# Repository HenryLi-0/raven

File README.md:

<div align="center">
    <h2>Raven</h2>
    <p>by <a href= "https://github.com/HenryLi-0/raven"> @HenryLi-0 </a></p>
    
</div>

<sub>It's open sourced! Hardware licensed under CERN OHL S v2. Software licensed under GNU GPL v3.</sub>

---

## Raven

[Raven](https://github.com/HenryLi-0/raven/) is an open source spinning LED light display, built for (and generously funded by) Hack Club's [Highway](https://highway.hackclub.com/)!

## Introduction
Since being introduced to an LED strip during FRC at the start of 2024, I realized I really like LEDs. Like a little too much. This could also be seen with the 10 LEDs from my [Hackpad](https://github.com/hackclub/hackpad/pull/224) back in October 2024 and when I brought it on a robotics trip to BattleCry in June 2025 (iykyk). Simply, I kinda like LEDs a lot. 

Now inspired by the lights at the venue of the aforementioned robotics trip (and the lights show that occured near the end of the event), that brings us here! Introducting Raven, a spinning LED display that uses 50 LEDs spread across 5 panels, spinning *really* fast. Using a Hall Effect Sensor for speed measurement, the measured values for angular prediction, and wireless control for wireless communications, Raven is capable of producing sector-based effects, rainbow gradients, strobes, and more, with a full 360 degree range of the room, or any sector of it! Apart from being an almost disco ball of sorts, the mechanism itself allows it to also act as an LED light display, almost looking like some sort of Vegas Sphere, except as a cylinder.

This project took over a hundred hours to make (with tons of redesigns!), and, retrospectively, I guess it's just because I think LEDs look pretty cool. The idea of replicating what happened in the venue really kept me going, and, now staring at what's been created, I think those hours were worth it! Learned lots a things along the way, such as reading datasheets, power in general, and implementing stuff from the ground up!

## Long Description

Incase you wanted a full, long description, here it is!

Introducing Raven, an open source spinning LED light display! The system can be separated into three parts: the motor subsystem, the LED control subsystem, and the LED panels. But first, what exactly is the idea behind Raven? Inspired by the light effects done at BattleCry 2025 at WPI (2025BC), along with really liking LEDs for some reason, I wanted to create a LED display that lights up an entire room. But a stationary system wouldn't create the desired effect, the effect to slice up the room into different colors. For example, imagine the left side of the room being red and the right being blue.

This is accomplished by having 5 LED panels, each with 10 LEDs each, vertically stacked, pointing outwards. These 5 panels form a 180 degree circle, each panel spaced 45 degrees off the next. Arms connecting to the top and bottom of the LED panels attach to a center. Spacers keep these top and bottom arms in position. In the center, the top arms connect to the LED control PCB, which contains a XIAO ESP32-C3. This board is also equipped with a Hall Effect Sensor, used to be a simple way to measure RPM without an expensive encoder. This entire section spins on a shaft collar connected to a 775 motor. Additionally, a 18650 Li-ion battery is on this section, powering the whole thing without need for a power wire.

In order to save on costs, a slip ring was strongly avoided during design. Instead, the motor subsystem powers the motor with 4 Li-ion batteries, supplying a total of 14.8-16.8V @20A to the motor. 4 Li-ion batteries was choosen as a solution to the problem with finding suitable boost converters, which were either incapable of handling 20A, or are just really expensive. In fact, it is actually cheaper to use 4 Li-ion batteries than a single one of these boost converters. This solution also gave the benefit of having additional battery time, which was a nice side bonus. The motor subsystem is stationary, with the base being a copy of the LED control subsystem's PCB. This empty PCB is used as the FR-4 material of the PCB is likely stronger than PLA parts, while also being a smart way to reuse the multiple PCBs sent by JLCPCB. This is also the reason why there are 5 LED panels, as to minimize waste. The motor subsystem is also powered with a XIAO ESP32-C3, and has its own Hall Effect Sensor to measure the RPM of the LED subsystem.

The control system starts at the stationary motor subsystem microcontroller, which sends a constant ping to the LED subsystem's microcontroller. The LED subsystem reads this ping through the ESP32's bluetooth capabilities, and also sends a ping back. Both systems need to listen to each other in order to think they are operating properly. In the event that a ping isn't heard in a long time, the LED subsystem will stop operating and the motor subsystem will attempt to bring the motor to a stop. While operating properly, the LED subsystem uses a mix of data from the motor subsystem's Hall Effect Sensor and the LED subsystem's Hall Effect Sensor to calculate its speed and position, utilizing a model of the motor's speed. The motor subsystem will use PID control with a MOSFET to ensure that the LED subsystem reaches the proper spin.

This entire system is packaged inside a cylinderical shape with diameter of roughly 24 cm and a height of roughly 15 cm. The LED subsystem, weighing less than 2 pounds, plans to spin at anywhere from 1k-2k RPM, in order to achieve a speed where the LEDs essentially blend into a blur. The LED subsytem is loaded with almost 120 screws, in order to ensure that the LED subsystem stays in place. Additionally, all batteries are protected inside an over-discharge protection board and charged with a TP4056 module with protection (the TP4056 does NOT provide power to the system, it is only used for charging.).

And that's Raven, an open source spinning light display!

## Directory

Wanna know more? Here's some quick places to get started!

- [CAD](</CAD/README.md>)
    - We used OnShape for this, but you can grab files here too! (Although, poking around the CAD is probably better to have an idea of what things look like!)
- [PCB](</PCB/README.md>)
    - We have three different PCBs, have a look at them! They were created in KiCad v8.0.8 (yeah I know I'm a whole major version behind.)
- [Firmware](</firmware/README.md>)
    - We have two firmwares, one for each subsystem! (These firmwares are written for CircuitPython! Look here for deeper instructions!)
- [Journal](</JOURNAL.md>)
    - Wanna know the thought process behind stuff? Or just a really long read? Check out the journal! (or the [`updatelogs`](/updatelogs/) for everything in different files...)
- [BOM](</BOM.csv>)
    - Wanna make your own copy of Raven? Here's the BOM in CSV format! (You can look at [`BOM.md`](</BOM.md>) for a markdown version of it, but it won't be too descriptive!) (Or just scroll down.)

---

---

## Assembly!

1. First things first, it's recommended that you pull up the [CAD](</CAD/README.md>) and get familiar with how things look, and think of the order of steps. Special attention should be paid towards making sure that it is possible to put together, along with wires being able to "fit". Use logic to figure out whether a wire will be inside a part!
2. We're gonna assemble all the PCBs first! Pull up the [PCB](</PCB/README.md>) on KiCad for the PCBs themselves. Where things should be placed should be clear in the drawing! Do NOT solder the Hall Effect Sensors on!
3. Test the boards! It'll be easier now before it's in an awkward position!
4. Back to the CAD, assemble the LED subsystem structure! This should be quite simple, but just very tedious, as there are are a lot of parts and screws.
5. Assemble the shaft collar and the motor subsystem structure!
6. Ok, place that all aside for now. It's time to do the power systems for both! While doing this, reference the electronics wiring drawn below! Also note the names of the nets in KiCad.
7. Check solder joints!!! Everything on the LED subsystem MUST be ziptied (or you will risk something flying off). After this, start finding the center of gravity of the LED subsystem and try to balance it in the center (important).
8. After this, assemble everything together! Note the CAD and the epic image above!
9. Test that each system works individually! If so, head on over to the [firmware](</firmware/README.md>) and flash both of them!
10. Enjoy and check back for any firmware/general updates!

## BOM
*The Bill of Materials for x1 unit of Raven!*

Note: For this list, the prices are as of July 2025. Depending on certain actions on certain people, this may fluctuate over the next couple months/years. Current calculations have shipping and tax included, but if you want to see how much everything actual ended up costing me (as in, trying to use all the deals), look out for `updatelogs` during construction time! If you'd like a BOM where things are grouped by type, check out [`BOM.md`](</BOM.md>). Check out ['BOM.csv`](</BOM.csv>) to also have descriptions of each item!

Try to use the AliExpress Welcome Deal on the 775 Motor and take advantage of a current sale on the batteries (drops all the batteries down to ~$26, including shipping and taxes)! (Batteries are currently calulated with the discount.)

| Part                          | Price         | Link              |
|-------------------------------|---------------|-------------------|
| M4 Screws (x20, 40mm)         | $2.85         | [AliExpress](https://www.aliexpress.us/item/3256804341271555.html) |
| M4 Screws (x20, 30mm)         | $2.49         | [AliExpress](https://www.aliexpress.us/item/3256804341271555.html) |
| M4 Screws (x80, 16mm)         | $7.96         | [AliExpress](https://www.aliexpress.us/item/3256804341271555.html) |
| M4 Nuts (x125)                | $9.45         | [AliExpress](https://www.aliexpress.us/item/3256807407546447.html) |
| 3D Printed Parts              | $0.00         | (self print)      |
| LED Panels (min 5)            | $2.10         | JLCPCB            |
| LED Subsystem (min 5)         | $4.00         | JLCPCB            |
| Motor Subsystem (min 5)       | $4.00         | JLCPCB            |
| Shipping (to NYC)             | $10.20        | JLCPCB            |
| XIAO ESP32-C3 (x2)            | $10.00        | [Seeed Studio](https://www.seeedstudio.com/Seeed-XIAO-ESP32C3-p-5431.html) |
| Shipping (to NYC)             | $9.00         | [Seeed Studio](https://www.seeedstudio.com/Seeed-XIAO-ESP32C3-p-5431.html) |
| A3144 (min 5)                 | $1.18         | [LCSC](https://lcsc.com/product-detail/Hall-Switches_JSMSEMI-A3144EUA-T-JSM_C18188954.html) |
| 30SQ045 (x3)                  | $1.76         | [LCSC](https://lcsc.com/product-detail/Schottky-Diodes_LGE-30SQ045_C2903878.html) |
| WS2812B (x65, mul 5)          | $4.28         | [LCSC](https://lcsc.com/product-detail/RGB-LEDs-Built-in-IC_Worldsemi-WS2812B-B-W_C114586.html) |
| 1N4148 (x2, min 20)           | $0.51         | [LCSC](https://lcsc.com/product-detail/Switching-Diodes_onsemi-1N4148_C258182.html) |
| PR01000101002JA100 (min 5)    | $0.60         | [LCSC](https://lcsc.com/product-detail/Through-Hole-Resistors_VISHAY-PR01000101002JA100_C1366567.html) |
| MF1W-100Ω±1% T (min 10)       | $0.45         | [LCSC](https://lcsc.com/product-detail/Through-Hole-Resistors_CCO-Chian-Chia-Elec-MF1W-100-1-T_C119469.html) |
| 1N5822 (x2, min 5)            | $0.51         | [LCSC](https://lcsc.com/product-detail/Schottky-Diodes_MDD-Microdiode-Semiconductor-1N5822_C2476.html) |
| AOD424 (x1)                   | $0.46         | [LCSC](https://lcsc.com/product-detail/MOSFETs_AOS-AOD424_C357852.html) |
| Handling Fee                  | $3.00         | (LCSC)            |
| Shipping (to NYC)             | $9.00         | (LCSC)            |
| 775 Motor (288W, 12k)         | $17.65        | [AliExpress](https://www.aliexpress.us/item/3256807114067845.html) |
| Overdischarge (1S 16A)        | $1.26         | [AliExpress](https://www.aliexpress.us/item/3256805852468677.html) |
| Overdischarge (4S 20A std.)   | $5.89         | [AliExpress](https://www.aliexpress.us/item/3256806720463818.html) |
| LM2596 (x1, Step Down)        | $1.76         | [AliExpress](https://www.aliexpress.us/item/3256805963034065.html) |
| XL6019 (x1, Step Up)          | $2.04         | [AliExpress](https://www.aliexpress.us/item/2255800011462620.html) |
| TP4056 (x5, USB-C, safety)    | $2.70         | [AliExpress](https://www.aliexpress.us/item/3256807959506419.html) |
| 22 AWG wire (5m, 1 roll)      | $2.02         | [AliExpress](https://www.aliexpress.us/item/3256807263561521.html) |
| 10 AWG wire (1m, Black)       | $6.86         | [AliExpress](https://www.aliexpress.us/item/3256807572728671.html) |
| Battery Holder (x2, 1B)       | $5.58         | [AliExpress](https://www.aliexpress.us/item/3256806864993334.html) |
| Battery Holder (x1, 4B)       | $3.72         | [AliExpress](https://www.aliexpress.us/item/3256806864993334.html) |
| Shipping (to NYC)             | $0.00         | (AliExpress)      |
| Samsung 25R 18650...          | $15.00        | [IMR Batteries](https://imrbatteries.com/products/samsung-25r-18650-2500mah-20a-battery) |
| Shipping (to NYC)             | $9.13         | (IMR Batteries)   |
| Taxes                         | $2.07         | (IMR Batteries)   |
| Buffer                        | $5.00         |                   |
| **TOTAL**                     | **$164.51**   |                   |

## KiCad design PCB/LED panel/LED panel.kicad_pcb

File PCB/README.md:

# PCB

This folder contains the PCB!

Checkout these folders!:
- [LED Subsystem](</PCB/led subsystem/>)
    - for the LED display logic (lots of LEDs!)
- [Motor Subsystem](</PCB/core/>)
    - for the logic and power controlling the motor (lots of power!)
- [LED Panel](</PCB/LED panel/>)
    - for the LED Panel (this is made 5 times!)

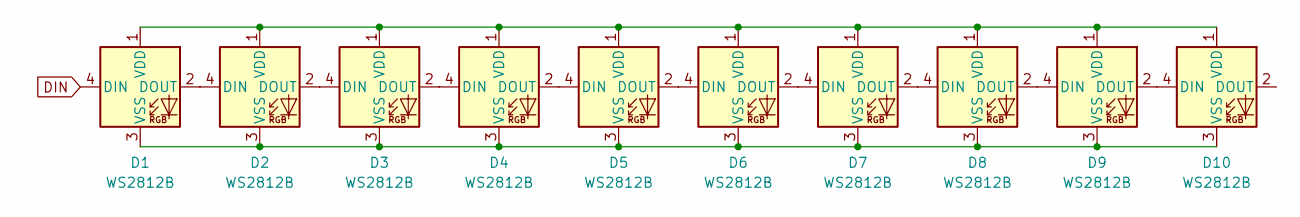
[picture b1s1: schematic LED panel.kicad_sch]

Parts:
D1, D2, D3, D4, D5, D6, D7, D8, D9, D10: WS2812B; LED_WS2812B_PLCC4_5.0x5.0mm_P3.2mm

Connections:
DIN: D1.4 (DIN)
unnamed: D1.2 (DOUT), D2.4 (DIN)
unnamed: D1.1 (VDD), D2.1 (VDD), D3.1 (VDD), D4.1 (VDD), D5.1 (VDD), D6.1 (VDD), D7.1 (VDD), D8.1 (VDD), D9.1 (VDD), D10.1 (VDD)
unnamed: D1.3 (VSS), D2.3 (VSS), D3.3 (VSS), D4.3 (VSS), D5.3 (VSS), D6.3 (VSS), D7.3 (VSS), D8.3 (VSS), D9.3 (VSS), D10.3 (VSS)
unnamed: D2.2 (DOUT), D3.4 (DIN)
unnamed: D3.2 (DOUT), D4.4 (DIN)
unnamed: D4.2 (DOUT), D5.4 (DIN)
unnamed: D5.2 (DOUT), D6.4 (DIN)
unnamed: D6.2 (DOUT), D7.4 (DIN)
unnamed: D7.2 (DOUT), D8.4 (DIN)
unnamed: D8.2 (DOUT), D9.4 (DIN)
unnamed: D9.2 (DOUT), D10.4 (DIN)

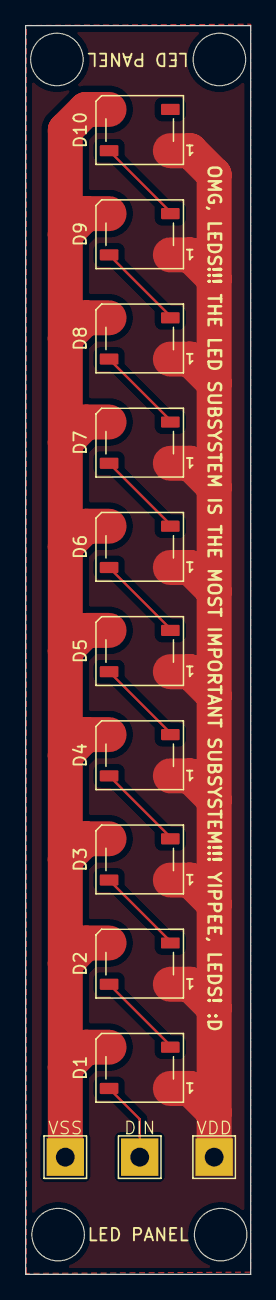
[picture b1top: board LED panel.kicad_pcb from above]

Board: 2 copper layers, 18.0 x 99.9 mm, 10 parts (0 on the bottom side), 11 nets.

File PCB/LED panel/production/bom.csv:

Designator,Footprint,Quantity,Value,LCSC Part #
"D1, D10, D2, D3, D4, D5, D6, D7, D8, D9",LED_WS2812B_PLCC4_5.0x5.0mm_P3.2mm,10,WS2812B,

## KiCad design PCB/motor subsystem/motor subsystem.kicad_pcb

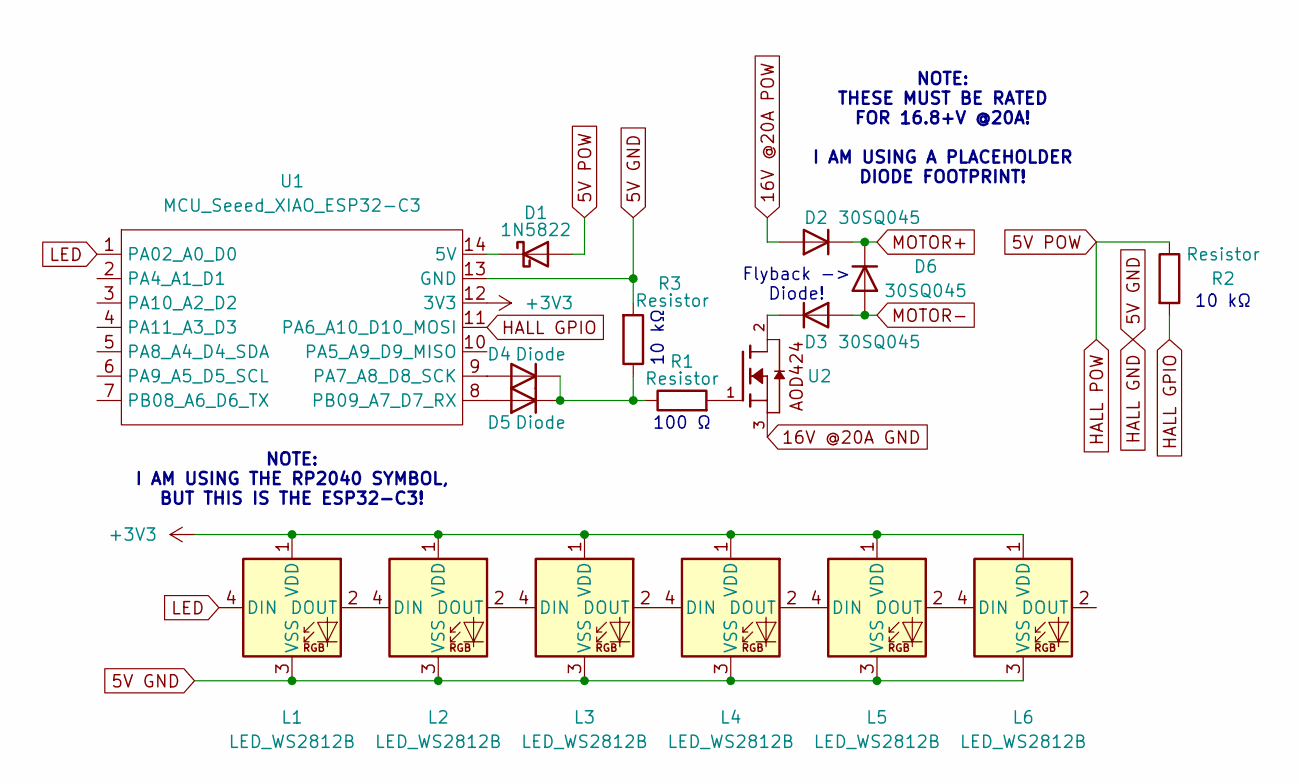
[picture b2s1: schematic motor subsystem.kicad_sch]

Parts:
D1: 1N5822; D_DO-201AD_P15.24mm_Horizontal
D2, D3, D6: 30SQ045; R_Axial_DIN0918_L18.0mm_D9.0mm_P25.40mm_Horizontal
D4, D5: Diode; Diode_DO-35
L1, L2, L3, L4, L5, L6: LED_WS2812B
R1: Resistor; R_Axial_DIN0411_L9.9mm_D3.6mm_P12.70mm_Horizontal
R2, R3: Resistor; R_Axial_DIN0411_L9.9mm_D3.6mm_P15.24mm_Horizontal
U1: MCU_Seeed_XIAO_ESP32-C3; Seeed_XIAO_RP2040
U2: AOD424

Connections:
5V GND: L1.3 (VSS), L2.3 (VSS), L3.3 (VSS), L4.3 (VSS), L5.3 (VSS), L6.3 (VSS), R3.2, U1.13 (GND)
5V POW: D1.2 (A), R2.1
16V @20A GND: U2.3
16V @20A POW: D2.2 (A)
+3V3: L1.1 (VDD), L2.1 (VDD), L3.1 (VDD), L4.1 (VDD), L5.1 (VDD), L6.1 (VDD), U1.12 (3V3)
HALL GPIO: R2.2, U1.11 (PA6_A10_D10_MOSI)
LED: L1.4 (DIN), U1.1 (PA02_A0_D0)
MOTOR+: D2.1 (K), D6.1 (K)
MOTOR-: D3.2 (A), D6.2 (A)
unnamed: D1.1 (K), U1.14 (5V)
unnamed: D3.1 (K), U2.2
unnamed: D4.2 (A), U1.9 (PA7_A8_D8_SCK)
unnamed: D4.1 (K), D5.1 (K), R1.1, R3.1
unnamed: D5.2 (A), U1.8 (PB09_A7_D7_RX)
unnamed: L1.2 (DOUT), L2.4 (DIN)
unnamed: L2.2 (DOUT), L3.4 (DIN)
unnamed: L3.2 (DOUT), L4.4 (DIN)
unnamed: L4.2 (DOUT), L5.4 (DIN)
unnamed: L5.2 (DOUT), L6.4 (DIN)
unnamed: R1.2, U2.1

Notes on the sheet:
10 kΩ
NOTE: THESE MUST BE RATED FOR 16.8+V @20A! I AM USING A PLACEHOLDER DIODE FOOTPRINT!
NOTE: I AM USING THE RP2040 SYMBOL, BUT THIS IS THE ESP32-C3!
Flyback -> Diode!
100 Ω

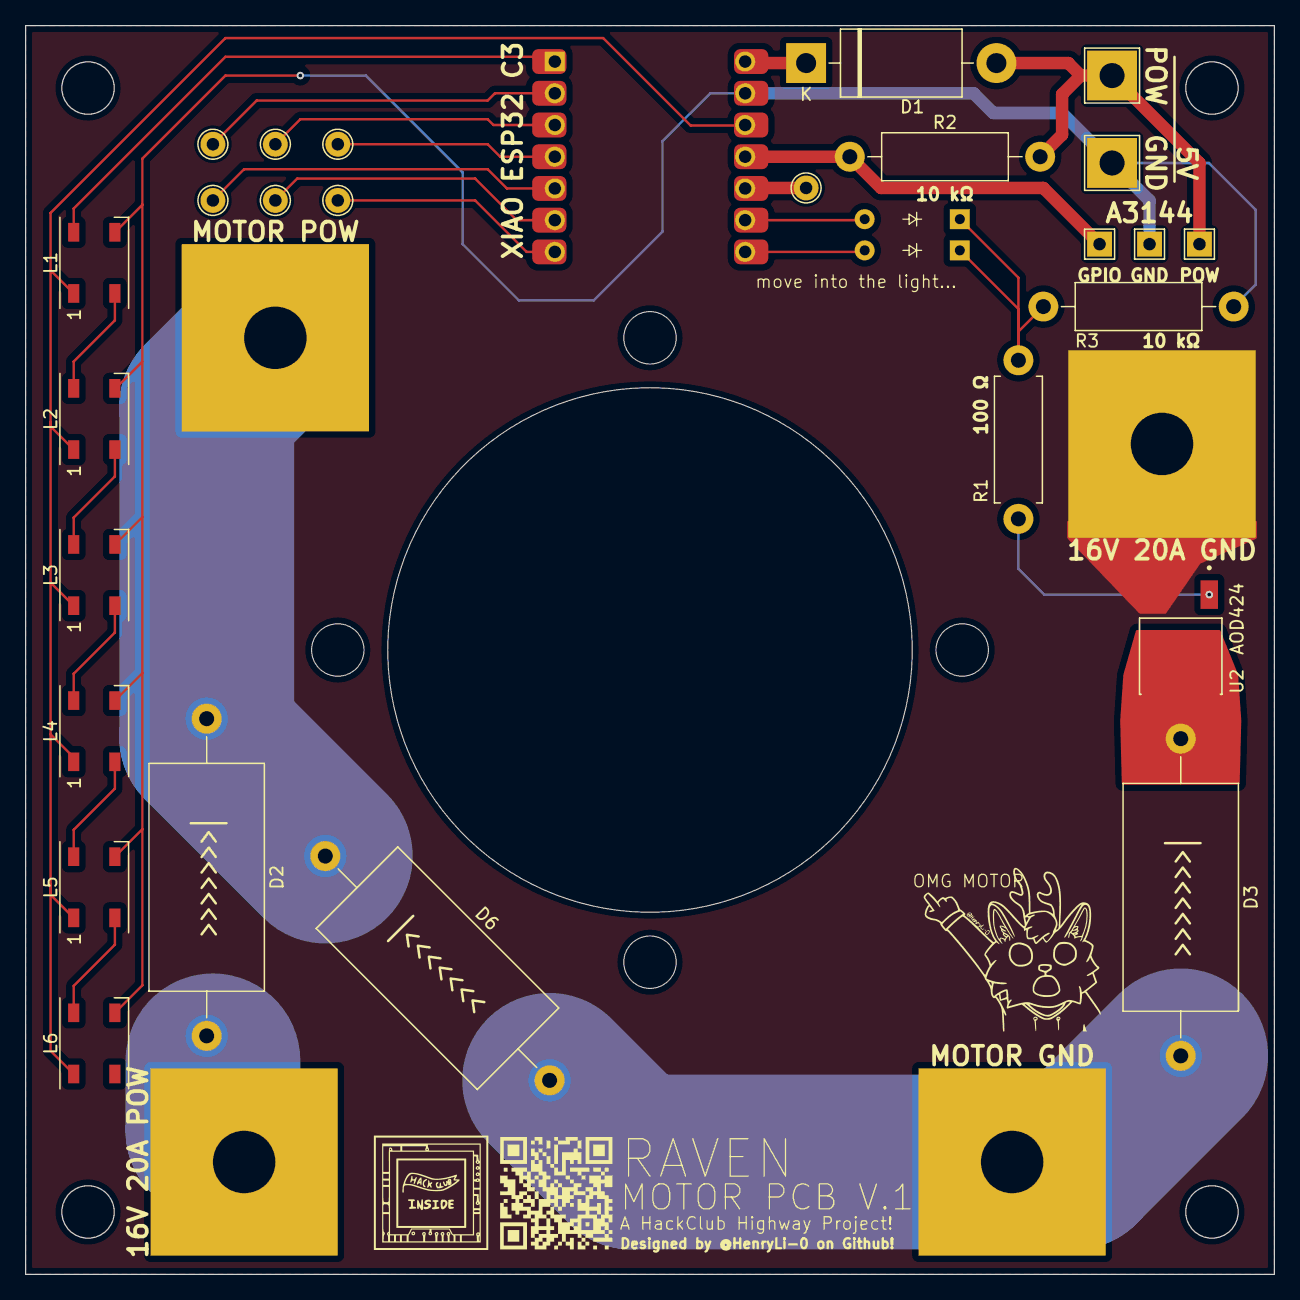
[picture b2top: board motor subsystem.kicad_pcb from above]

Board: 2 copper layers, 100.0 x 100.0 mm, 17 parts (0 on the bottom side), 18 nets.

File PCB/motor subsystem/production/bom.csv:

Designator,Footprint,Quantity,Value,LCSC Part #
"_4, _3, _2, ",,4,,
D1,D_DO-201AD_P15.24mm_Horizontal,1,1N5822,
"D2, D3, D6",R_Axial_DIN0918_L18.0mm_D9.0mm_P25.40mm_Horizontal,3,30SQ045,
"D4, D5",Diode_DO-35,2,Diode,
"L1, L2, L3, L4, L5, L6",LED_WS2812B,6,LED_WS2812B,
R1,R_Axial_DIN0411_L9.9mm_D3.6mm_P12.70mm_Horizontal,1,Resistor,
"R2, R3",R_Axial_DIN0411_L9.9mm_D3.6mm_P15.24mm_Horizontal,2,Resistor,
U1,Seeed_XIAO_RP2040,1,MCU_Seeed_XIAO_ESP32-C3,
U2,AOD424,1,~,

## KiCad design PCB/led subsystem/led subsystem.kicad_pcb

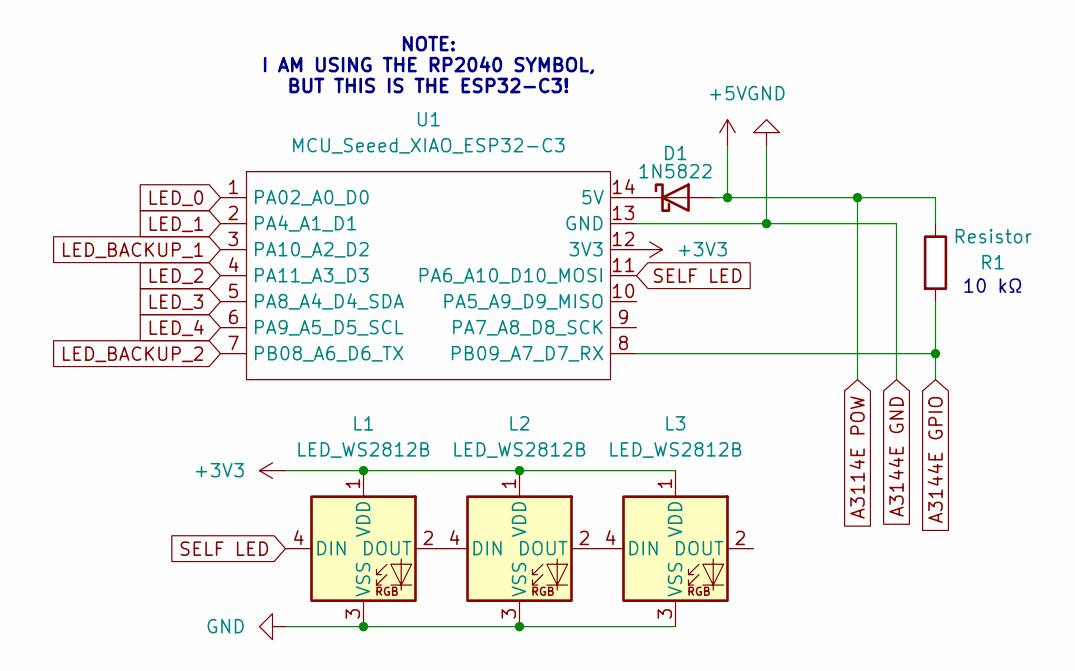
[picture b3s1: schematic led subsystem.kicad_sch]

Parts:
D1: 1N5822; D_DO-201AD_P15.24mm_Horizontal
L1, L2, L3: LED_WS2812B
R1: Resistor; R_Axial_DIN0411_L9.9mm_D3.6mm_P15.24mm_Horizontal
U1: MCU_Seeed_XIAO_ESP32-C3; Seeed_XIAO_RP2040

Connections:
+3V3: L1.1 (VDD), L2.1 (VDD), L3.1 (VDD), U1.12 (3V3)
A3114E POW: D1.2 (A), R1.1
A3144E GND: L1.3 (VSS), L2.3 (VSS), L3.3 (VSS), U1.13 (GND)
A3144E GPIO: R1.2, U1.8 (PB09_A7_D7_RX)
LED_0: U1.1 (PA02_A0_D0)
LED_1: U1.2 (PA4_A1_D1)
LED_2: U1.4 (PA11_A3_D3)
LED_3: U1.5 (PA8_A4_D4_SDA)
LED_4: U1.6 (PA9_A5_D5_SCL)
LED_BACKUP_1: U1.3 (PA10_A2_D2)
LED_BACKUP_2: U1.7 (PB08_A6_D6_TX)
unnamed: D1.1 (K), U1.14 (5V)
unnamed: L1.2 (DOUT), L2.4 (DIN)
unnamed: L2.2 (DOUT), L3.4 (DIN)
SELF LED: L1.4 (DIN), U1.11 (PA6_A10_D10_MOSI)

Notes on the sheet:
10 kΩ
NOTE: I AM USING THE RP2040 SYMBOL, BUT THIS IS THE ESP32-C3!

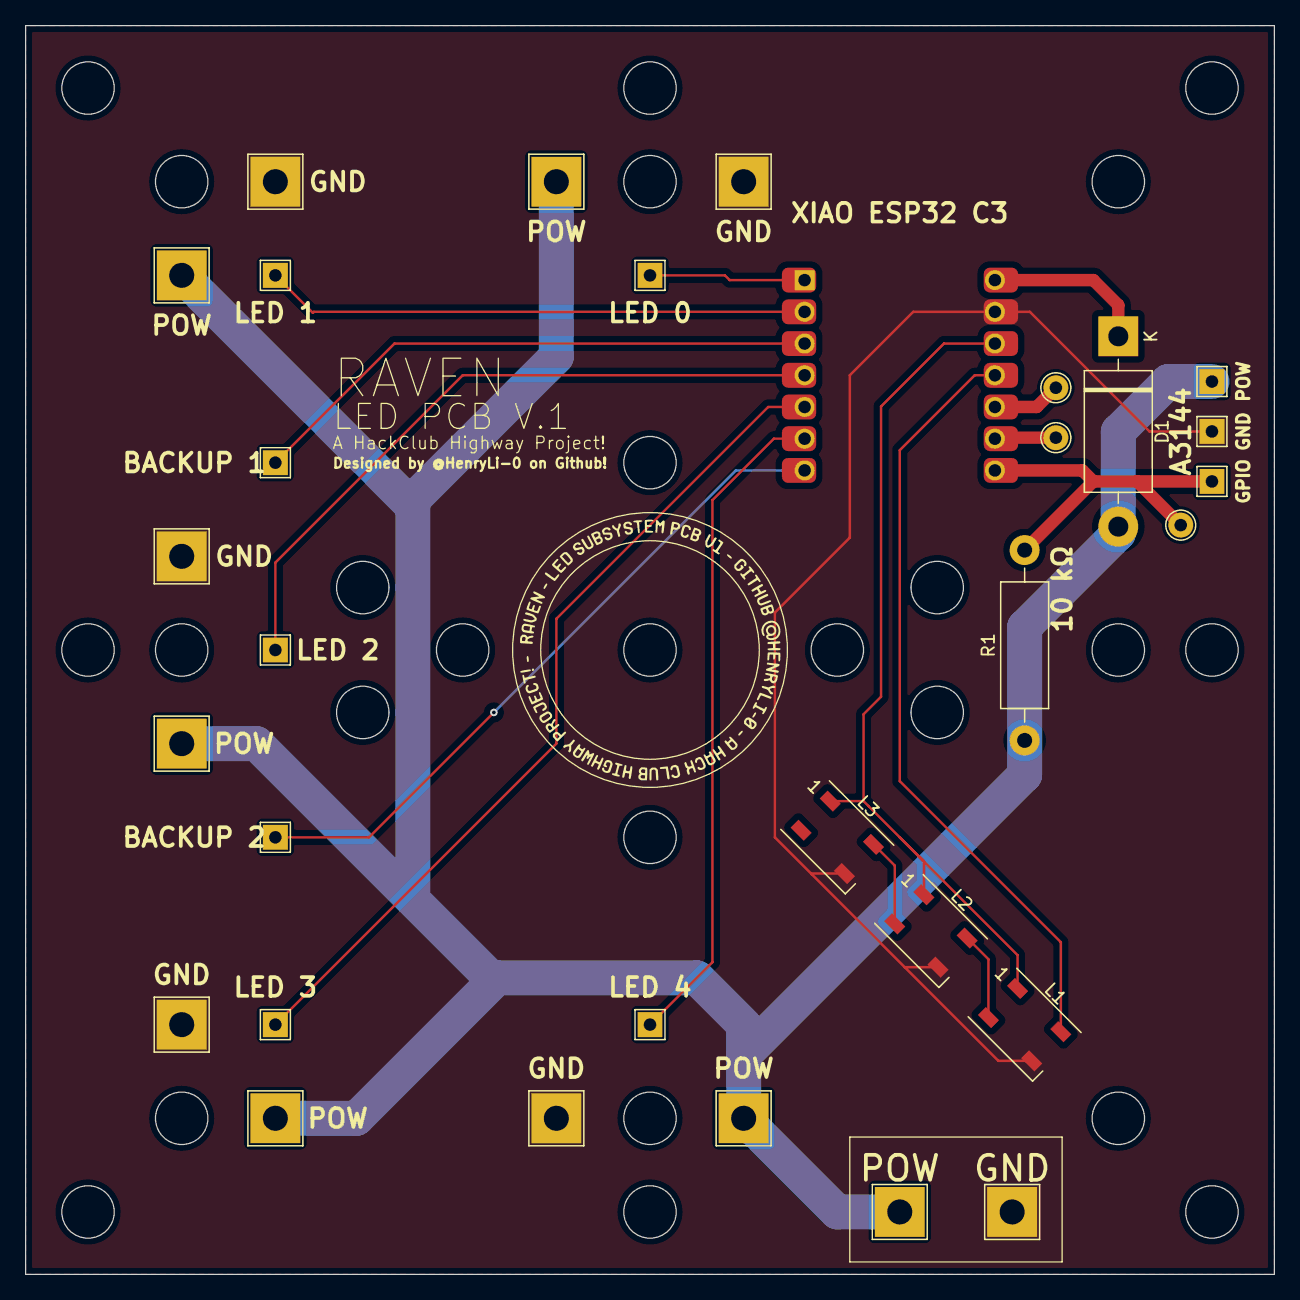
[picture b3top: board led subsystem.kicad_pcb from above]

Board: 2 copper layers, 100.0 x 100.0 mm, 6 parts (0 on the bottom side), 8 nets.

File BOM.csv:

Part,Description,Quantity,Price,Source,Link
M4 Screws (40mm),Structural,20, $2.85 ,AliExpress,https://www.aliexpress.us/item/3256804341271555.html
M4 Screws (30mm),Structural,20, $2.49 ,AliExpress,https://www.aliexpress.us/item/3256804341271555.html
M4 Screws (16mm),Structural,80, $7.96 ,AliExpress,https://www.aliexpress.us/item/3256804341271555.html
M4 Nuts,Structural,125, $9.45 ,AliExpress,https://www.aliexpress.us/item/3256807407546447.html
3D Printed Parts,Structural,NA, $-   ,Self Printing,NA
PCB LED Panels,Rotating LED Panels,5, $2.10 ,JLCPCB,https://jlcpcb.com/
PCB LED Subsystem,LED Subsystem Control PCB (rotates),5, $4.00 ,JLCPCB,https://jlcpcb.com/
PCB Motor Subsystem,Motor Subsystem Control PCB (stationary),5, $4.00 ,JLCPCB,https://jlcpcb.com/
PCB Shipping (JLCPCB -> NYC),Shipping,NA, $10.20 ,JLCPCB,NA
SeeedStudio XIAO ESP32-C3,Microcontrollers,2, $10.00 ,SeeedStudio,https://www.seeedstudio.com/Seeed-XIAO-ESP32C3-p-5431.html
SeeedStudio Shipping (Warehouse -> NYC),Shipping,NA, $9.00 ,SeeedStudio,NA
A3144,Hall Effect Sensors,5, $1.18 ,LCSC,https://lcsc.com/product-detail/Hall-Switches_JSMSEMI-A3144E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
30SQ045,Motor Diodes,3, $1.76 ,LCSC,https://lcsc.com/product-detail/Schottky-Diodes_LGE-30SQ045_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
WS2812B,LEDs,65, $4.28 ,LCSC,https://lcsc.com/product-detail/RGB-LEDs-Built-in-IC_Worldse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
1N4148,Logic Diodes,20, $0.51 ,LCSC,https://lcsc.com/product-detail/Switching-Diodes_onsemi-1N41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
PR01000101002JA100,10 kΩ Resistor,5, $0.60 ,LCSC,https://lcsc.com/product-detail/Through-Hole-Resistors_VISHA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
MF1W-100Ω±1% T,100 Ω Resistor,10, $0.45 ,LCSC,https://lcsc.com/product-detail/Through-Hole-Resistors_CCO-C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
1N5822,Microcontroller Schottky Diodes,5, $0.51 ,LCSC,https://lcsc.com/product-detail/Schottky-Diodes_MDD-Microdio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
LCSC Handling Fee,Some Fee,NA, $3.00 ,LCSC,NA
LCSC Shipping (LCSC -> NYC),Shipping,NA, $9.00 ,LCSC,NA
"775 Motor (288W, 12k)",The Motor Behind It All,1, $17.65 ,AliExpress,https://www.aliexpress.us/item/3256807114067845.html
Overdischarge Protection (1S 16A),Protects batteries from overdischarge (safety),1, $1.26 ,AliExpress,https://www.aliexpress.us/item/3256805852468677.html
Overdischarge Protection (4S 20A Standard),Protects batteries from overdischarge (safety),1, $5.89 ,AliExpress,https://www.aliexpress.us/item/3256806720463818.html
LM2596 (Step Down Converter),Steps down voltage for Motor Subsystem,1, $1.76 ,AliExpress,https://www.aliexpress.us/item/3256805963034065.html
XL6019 (Step Up Converter),Steps up voltage for LED Subsystem,1, $2.04 ,AliExpress,https://www.aliexpress.us/item/2255800011462620.html
"TP4056 (USB-C, Safety)",Recharges batteries (SAFETY VERSION NEEDED),5, $2.70 ,AliExpress,https://www.aliexpress.us/item/3256807959506419.html
"22 AWG wire (5m, 1 roll)",Wires for LED subsystem -> LED panels,1, $2.02 ,AliExpress,https://www.aliexpress.us/item/3256807263561521.html
"10 AWG wire (1m, Black)",Wires for Motor subsystem,1, $6.86 ,AliExpress,https://www.aliexpress.us/item/3256807572728671.html
Samsung 25R 18650 2500mAh 20A Battery,Batteries for the whole system,5, $15.00 ,IMR Batteries,https://imrbatteries.com/products/samsung-25r-18650-2500mah-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
Taxes,Mysterious IMR Batteries Taxes,NA, $2.10 ,IMR Batteries,NA
Battery Shipping (IMR Batteries -> NYC),Shipping,NA, $9.13 ,IMR Batteries,NA
Buffer,"In the event of mysterious price increases/errors in calculations (there probably isn't, but just in case)",NA, $5.00 ,NA,NA
Total,,, $154.75 ,,

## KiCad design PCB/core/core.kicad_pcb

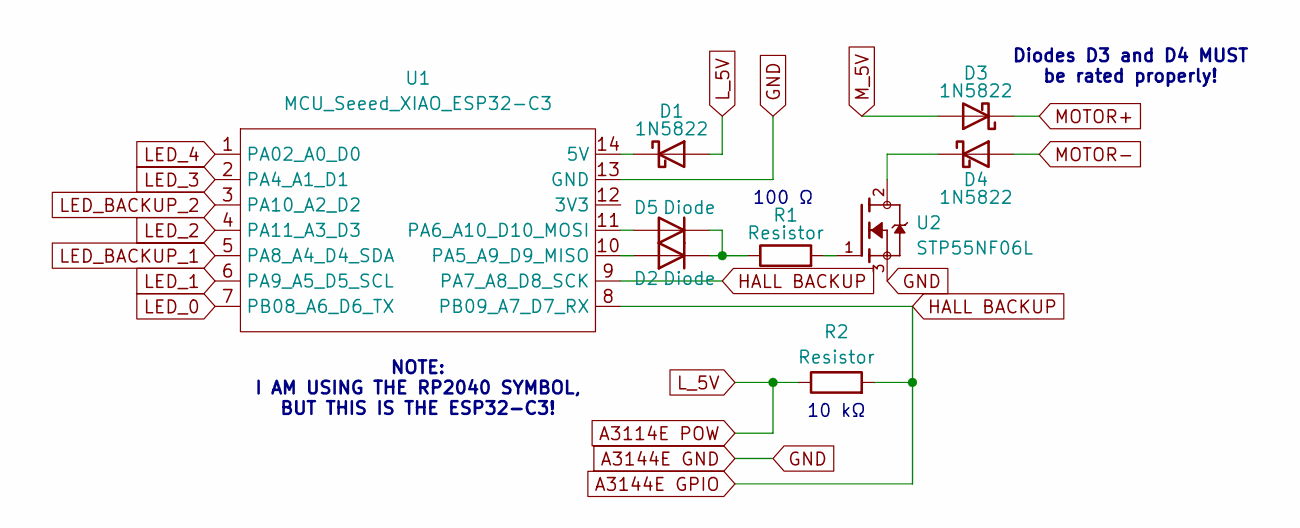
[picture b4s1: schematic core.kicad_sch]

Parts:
D1, D3, D4: 1N5822; D_DO-201AD_P15.24mm_Horizontal
D2, D5: Diode; Diode_DO-35
R1: Resistor; R_Axial_DIN0411_L9.9mm_D3.6mm_P20.32mm_Horizontal
R2: Resistor; R_Axial_DIN0411_L9.9mm_D3.6mm_P15.24mm_Horizontal
U1: MCU_Seeed_XIAO_ESP32-C3; Seeed_XIAO_RP2040
U2: STP55NF06L; TO254P1040X460X1935-3

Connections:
A3114E POW: D1.2 (A), R2.1
A3144E GND: U1.13 (GND), U2.3
A3144E GPIO: R2.2, U1.8 (PB09_A7_D7_RX), U1.9 (PA7_A8_D8_SCK)
LED_0: U1.7 (PB08_A6_D6_TX)
LED_1: U1.6 (PA9_A5_D5_SCL)
LED_2: U1.4 (PA11_A3_D3)
LED_3: U1.2 (PA4_A1_D1)
LED_4: U1.1 (PA02_A0_D0)
LED_BACKUP_1: U1.5 (PA8_A4_D4_SDA)
LED_BACKUP_2: U1.3 (PA10_A2_D2)
MOTOR+: D3.1 (K)
MOTOR-: D4.2 (A)
M_5V: D3.2 (A)
unnamed: D1.1 (K), U1.14 (5V)
unnamed: D2.2 (A), U1.10 (PA5_A9_D9_MISO)
unnamed: D2.1 (K), D5.1 (K), R1.1
unnamed: D4.1 (K), U2.2
unnamed: D5.2 (A), U1.11 (PA6_A10_D10_MOSI)
unnamed: R1.2, U2.1

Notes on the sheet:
10 kΩ
NOTE: I AM USING THE RP2040 SYMBOL, BUT THIS IS THE ESP32-C3!
Diodes D3 and D4 MUST be rated properly!
100 Ω

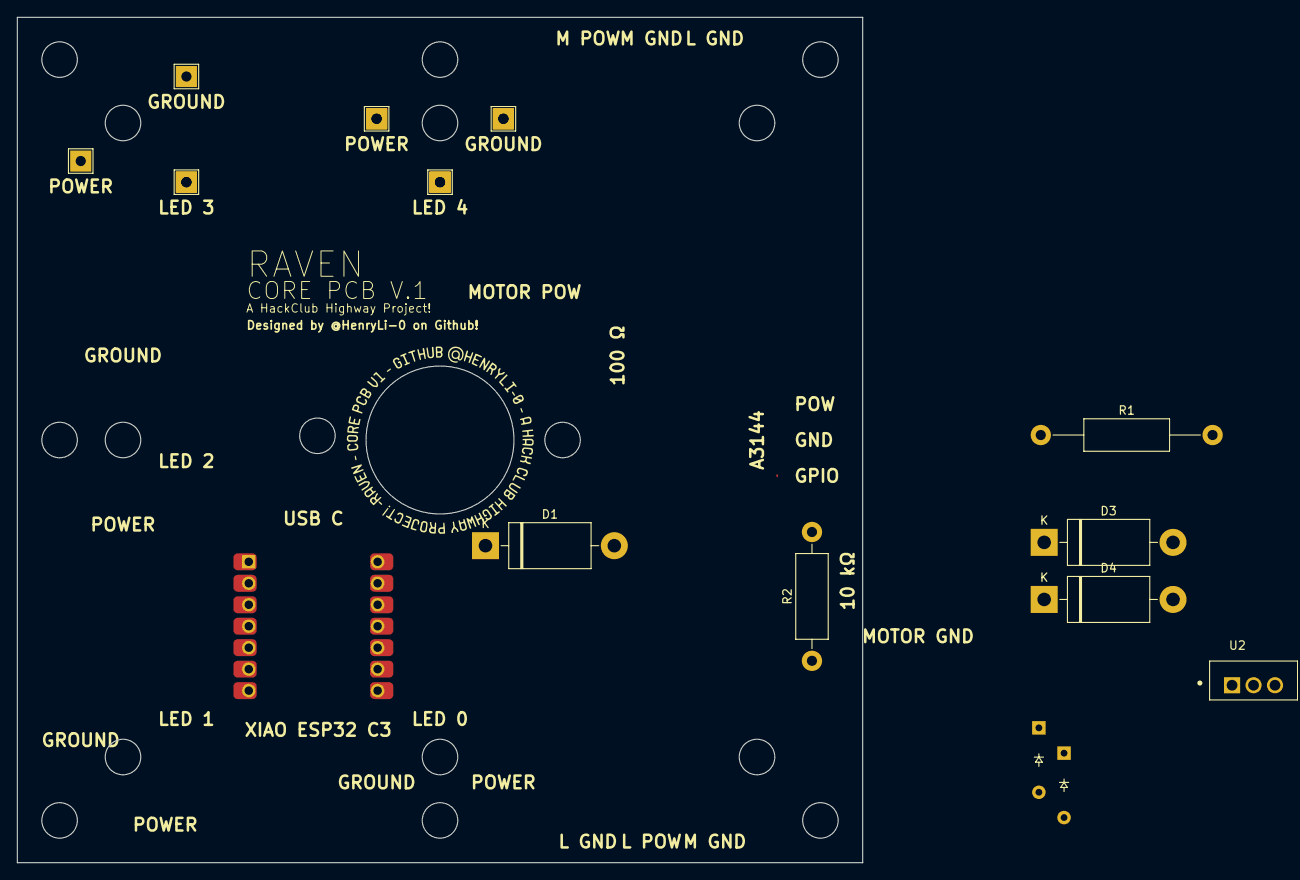
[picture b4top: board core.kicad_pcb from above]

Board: 2 copper layers, 100.0 x 100.0 mm, 9 parts (0 on the bottom side), 9 nets.

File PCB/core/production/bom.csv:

Designator,Footprint,Quantity,Value,LCSC Part #
"D1, D3, D4",D_DO-201AD_P15.24mm_Horizontal,3,1N5822,
D2,Diode_DO-35,1,Diode,
R1,R_Axial_DIN0411_L9.9mm_D3.6mm_P20.32mm_Horizontal,1,Resistor,
R2,R_Axial_DIN0411_L9.9mm_D3.6mm_P15.24mm_Horizontal,1,Resistor,
U1,Seeed_XIAO_RP2040,1,MCU_Seeed_XIAO_ESP32-C3,
U2,TO254P1040X460X1935-3,1,STP55NF06L,

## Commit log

2025-06-25 readme!
2025-06-26 add folders
2025-06-27 06252025 and 06262025! ideas and tests!
2025-06-28 06272025 - really refining the idea more!
2025-06-29 lots of part researching, wiring too!
2025-06-29 06282025 - parts found and starting pcb!
2025-06-29 LED panel PCB!
2025-06-30 core PCB!!!
2025-06-30 06292025 - pcb work!!!
2025-06-30 journal update! (yep im not asleep yet)
2025-06-30 start firmware (and heading off to bed)
2025-07-01 06302025 - starting CAD!
2025-07-02 07012025 - pcb updates and some cad work!
2025-07-03 07022025 - cad work! (hehe funny mount)
2025-07-04 fix folder structure oops
2025-07-04 07032025 - even more cad work!
2025-07-04 licenses!
2025-07-04 update led panel and step files
2025-07-04 testing and moving stuff around in cad
2025-07-05 07042025 - pcb, licenses, and confusion
2025-07-06 further confusion (get it? (search it up!))
2025-07-06 07052025 - further confusion
2025-07-07 rest of 7/5/2025
2025-07-07 research for overdischarge protection!
2025-07-07 lcsc hunting
2025-07-07 touching grass but still looking at LED/
2025-07-08 07072025 - leds and drawings
2025-07-08 update journal (with 7/6/2025 and 7/7/2025)!
2025-07-09 updated led panel
2025-07-09 im tired
2025-07-09 07082025 - confusion and maybe ideas
2025-07-10 07092025 - struggles finding a boost converter
2025-07-11 batteries
2025-07-11 07102025 - not much, drawing and finding parts and thinking
2025-07-12 update journal (with 7/8/2025-7/10/2025)!
2025-07-12 plan and electronics drawing! AND LEDS!!!
2025-07-12 07112025 - plans and start new PCBs!
2025-07-12 updated LED panel ground fill pour
2025-07-13 07122025 - firmware plans and two PCBs in one day!
2025-07-13 update motor PCB for hall effect sensor and other stuff
2025-07-13 start led subsystem firmware!
2025-07-13 restructure led firmware file structure
2025-07-13 start motor subsystem firmware!
2025-07-14 07132025 - finishing PCBs, starting firmware, updating/working on CAD!
2025-07-14 update journal (with 7/11/2025-7/13/2025)!
2025-07-15 lots of CAD progress!
2025-07-15 07142025 - lots of cad stuff!
2025-07-17 cad, screws, and mounting holes!
2025-07-17 07162025 - cad cad cad
2025-07-18 07172025 - wrapping up CAD!
2025-07-19 07182025 - almost done with CAD, lots of writing!
2025-07-20 update journal (with 7/14/2025-7/18/2025)!
2025-07-20 07192025 - finishing cad and start bom
2025-07-21 mosfet nightmares and cad
2025-07-21 07202025 - mosfet nightmares, cad, and firmware!
2025-07-21 some led firmware work!
2025-07-22 led subsystem firmware!
2025-07-22 some motor subsystem firmware code!
2025-07-22 07212025 - FIRMWARE AND CAD WOO
2025-07-23 07222025 - checks and a MOSFET!
2025-07-24 07232025 - mosfet added and writing BOM!
2025-07-25 motor pcb edits
2025-07-25 07242025 - parts and almost finishing BOM!
2025-07-25 update journal (with 7/19/2025-7/24/2025)!
2025-07-26 most of BOM
2025-07-26 prepare for future bluetooth implemenation!
2025-07-26 07252025 - almost there!
2025-07-27 update stuff and blender things!
2025-07-27 fixed banner?
2025-07-27 more writing, instructions, and battery cases added!
2025-07-27 07262025 - there!
2025-07-27 add long description
2025-07-27 typo fix and add another batter holder (for charger) to bom
2025-07-27 add pcb images
2025-07-27 add cad and compress readme bom
2025-07-27 move readme images into their own folder
2025-07-28 07272025 - submitting!
2025-07-29 07282025 - buying parts!
2025-07-30 07292025 - 3d printing!
2025-07-30 move 3mf files into their own folder!
2025-07-31 07302025 - more 3d printing!
2025-08-01 07312025 - waiting for packages!
2025-08-02 08012025 - microcontrollers came!
2025-08-02 playing around with sockets!
2025-08-03 08022025 - playing around with microcontroller and wifi!
2025-08-05 08042025 - batteries arrived!
2025-08-07 08062025 - lcsc stuff arrived!
2025-08-08 08072025 - all packages here and 3d printing!
2025-08-09 08082025 - construction day 1, lots of tapping!
2025-08-11 08102025 - construction day 2 and fixing motor support shield issue (hopefully)!
2025-08-12 08112025 - construction day 3!
2025-08-13 08122025 - electronics day 1!
2025-08-19 08182025 - soldering some leds for motor subsystem pcb
